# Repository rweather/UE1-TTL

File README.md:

UE1 Computer in TTL
===================

## What is this?

This is an implementation of the [Usagi Electric UE1 vacuum tube computer architecture](https://github.com/Nakazoto/UEVTC/wiki)
in TTL logic.  It runs the same code as the original.

Here is the top and bottom of the version 1 prototype, just after running the
Fibonacci example (click for a larger image):

I made some mistakes in the version 1 prototype that needed bodging.
The schematics and gerbers below have been updated to include the fixes.

## Specifications

* TTL logic, 555 timers, and EEPROM chips only.  No cheating with a modern
  microcontroller running an emulator.
* 1-bit processor core based on the UE14500 instruction set.
* 8-bit scratch register (general-purpose RAM).
* 8-bit output register.
* 7-bit input register.
* EEPROM that stores up to 8 program "tapes", each up to 4096 instructions.
  DIP switches select which program to run.
* 555-based clock that runs at frequencies between 0.7Hz and 480Hz.
* Run, Halt, and Reset buttons to control the computer.
* Blinkenlichten!
* Bell buzzer.
* Runs off a single 5V DC supply.

The computer is split across three PCB's, because:

* PCB's less than 100mm x 100mm in size are cheaper to get made.
* The aspect ratio of the boards is close to those of the wooden backing
  boards in the original UE1 to provide a similar visual aesthetic
  (although I need 3 boards compared with the original 2).
* It is easier to upgrade one of the boards without having to re-spin
  the other boards.

## Technical information

* [Theory of operation](doc/theory_of_operation.md)
* [Signals on the edge connectors](doc/edge_connectors.md)

### Clock and front panel board

* [Schematics](schematics/UE1-TTL-Clock/PDF/UE1-TTL-Clock.pdf)
* [Gerbers](schematics/UE1-TTL-Clock/Gerber)
* [Assembling and testing](doc/testing_clock.md)
* [Version 1 mistakes](doc/testing_clock.md#version-1-mistakes)

### Processor board

* [Schematics](schematics/UE14500-TTL/PDF/UE14500-TTL.pdf)
* [Gerbers](schematics/UE14500-TTL/Gerber)
* [Assembling and testing](doc/testing_processor.md)
* [Version 1 mistakes](doc/testing_processor.md#version-1-mistakes)

### Memory and I/O board

* [Schematics](schematics/UE1-TTL-Memory/PDF/UE1-TTL-Memory.pdf)
* [Gerbers](schematics/UE1-TTL-Memory/Gerber)
* [Assembling and testing](doc/testing_memory.md)
* [Version 1 mistakes](doc/testing_memory.md#version-1-mistakes)

## Programming the computer

To reprogram the computer it is necessary to remove the 32K AT28C256 tape
EEPROM from the memory board and flash in a new set of tape images using an
EEPROM programmer.

There can be up to 8 programs in the EEPROM, with DIP switches to select
which program to run.  Each program is up to 4096 instructions long,
which corresponds to about 10m of paper tape.  Each instruction consists
of a 4-bit opcode and a 4-bit memory address just like in the vacuum tube
based UE1.

Pad shorter programs with NOP0 instructions or replicate the program
multiple times to fill up the 4096 bytes of space.  There is a new
"rewind" opcode that can be used to loop short programs without
excessive NOP0's.  See the next section.

The "programs" directory contains some sample programs, together with a
Python script to pack up to 8 binaries into a single 32K EEPROM image.

## Instruction set

This computer uses the same [instruction set](https://github.com/Nakazoto/UEVTC/wiki/UE14500-Processor)
as the original computer.  The only difference is the introduction of a
"rewind" opcode which is encoded as "NOP0" with a memory address between
8 and 15 - bytes $08 to $0F in hexadecimal.

The rewind opcode causes the 12-bit program counter to reset back to 0
immediately, rather than waiting for the program counter to wrap around.
This can be convenient for short looping programs to avoid a long wait
for the loop to restart.

## Parts lists

In the parts lists below, "RLED" refers to the inline series resistor
for the LED's.  The value depends upon the type of LED you have, and can
be calculated from the LED's voltage drop (VLED) and rated current (ILED)
as follows:

    RLED = (5 - VLED) / ILED

For example, if your LED is rated for 1.9V and 10mA, then RLED should be
at least (5 - 1.9) / 0.01 = 310 ohms.  A 330 ohm resistor will do.
I recommend using LED's with 2mA or less current rating to avoid putting
too much strain on the TTL logic outputs.  I used 2mA LED's and RLED =
1800 ohms.

The IC's are listed as 74LS series, but you can use 74HC series instead.
Use the same series for all chips.

Parts lists for individual boards are listed first, and then a combined
parts list for the whole computer.

### Clock and front panel board

* 2 x 555 timer
* 1 x 74HC4017 decade counter
* 1 x 74LS74 dual D flip-flop
* 1 x 74LS02 quad NOR gate
* 1 x 74LS132 quad NAND gate with Schmitt trigger
* 2 x 10nF ceramic or monolithic capacitor
* 4 x 100nF ceramic or monolithic capacitor
* 4 x 1uF ceramic or monolithic capacitor
* 1 x 1M trimpot
* 2 x 1K resistor
* 1 x 3K3 resistor
* 1 x 4K7 resistor
* 1 x 10K resistor
* 1 x 100K resistor
* 22 x RLED resistor
* 22 x 3mm LED (colour of your choice)
* 1 x Buzzer with 7.6mm pin pitch
* 3 x 6mm momentary push button
* 1 x 3-way 2.54mm pin header
* 1 x 2-way 2.54mm pin header
* 2 x 2.54mm jumper
* 2 x 36-pin right-angle terminal header
* 2 x 8-pin DIP socket
* 3 x 14-pin DIP socket
* 1 x 16-pin DIP socket

### Processor board

* 3 x 74LS00 quad NAND gate
* 3 x 74LS02 quad NOR gate
* 2 x 74LS08 quad AND gate
* 3 x 74LS74 dual D flip-flop
* 1 x 74LS86 quad XOR gate
* 2 x 74LS138 3-to-8 line decoder
* 1 x 74LS251 8-line to 1-line multiplexer
* 1 x 74LS374 8-bit register
* 1 x 100uF electrolytic capacitor
* 1 x 1uF ceramic or monolithic capacitor
* 16 x 100nF ceramic or monolithic capacitor
* 1 x 10K resistor
* 1 x SPDT 2.54mm slide switch
* 1 x 2.5mm DC barrel jack
* 2 x 36-pin right-angle terminal socket
* 12 x 14-pin DIP socket
* 3 x 16-pin DIP socket
* 1 x 20-pin DIP socket

### Memory and I/O board

* 1 x AT28C256 32K x 8 EEPROM
* 1 x 74LS32 quad OR gate
* 1 x 74LS139 dual 2-to-4 line decoder
* 2 x 74LS251 8-line to 1-line multiplexer
* 2 x 74LS259 8-bit addressable latch
* 2 x 74LS393 dual binary 4-bit counter
* 9 x 100nF ceramic or monolithic capacitor
* 1 x 10K resistor
* 10 x 100K resistor
* 8 x RLED resistor
* 8 x 3mm LED (colour of your choice)
* 1 x 8-way DIP switches
* 1 x 3-way DIP switches
* 2 x 36-pin right-angle terminal header
* 3 x 14-pin DIP socket
* 5 x 16-pin DIP socket
* 1 x 28-pin DIP socket (15.24mm pitch width)

I recommend using a socket for the 28-pin EEPROM even if you don't use
sockets for the other chips.  You will need to easily remove the EEPROM to
reprogram it.

## Combined part list

This section combines all three lists into one to make it easier to
order the parts for the whole computer.  As stated before, 74HC series
chips can be used in place of 74LS.

* 1 x AT28C256 32K x 8 EEPROM
* 2 x 555 timer
* 1 x 74HC4017 decade counter
* 3 x 74LS00 quad NAND gate
* 4 x 74LS02 quad NOR gate
* 2 x 74LS08 quad AND gate
* 1 x 74LS32 quad OR gate
* 4 x 74LS74 dual D flip-flop
* 1 x 74LS86 quad XOR gate
* 1 x 74LS132 quad NAND gate with Schmitt trigger
* 2 x 74LS138 3-to-8 line decoder
* 1 x 74LS139 dual 2-to-4 line decoder
* 3 x 74LS251 8-line to 1-line multiplexer
* 2 x 74LS259 8-bit addressable latch
* 1 x 74LS374 8-bit register
* 2 x 74LS393 dual binary 4-bit counter
* 1 x 100uF electrolytic capacitor
* 5 x 1uF ceramic or monolithic capacitor
* 2 x 10nF ceramic or monolithic capacitor
* 29 x 100nF ceramic or monolithic capacitor
* 1 x 1M trimpot
* 2 x 1K resistor
* 1 x 3K3 resistor
* 1 x 4K7 resistor
* 3 x 10K resistor
* 11 x 100K resistor
* 30 x RLED resistor
* 30 x 3mm LED (colour of your choice)
* 1 x SPDT 2.54mm slide switch
* 1 x 2.5mm DC barrel jack
* 1 x Buzzer with 7.6mm pin pitch
* 3 x 6mm momentary push button
* 1 x 3-way 2.54mm pin header
* 1 x 2-way 2.54mm pin header
* 2 x 2.54mm jumper
* 1 x 8-way DIP switches
* 1 x 3-way DIP switches
* 4 x 36-pin terminal header (for clock and memory boards)
* 2 x 36-pin terminal socket (for CPU board)
* 2 x 8-pin DIP socket
* 18 x 14-pin DIP socket
* 9 x 16-pin DIP socket
* 1 x 20-pin DIP socket
* 1 x 28-pin DIP socket (15.24mm pitch width)

I recommend using a socket for the 28-pin EEPROM even if you don't use
sockets for the other chips.  You will need to easily remove the EEPROM to
reprogram it.

## License

<p xmlns:cc="http://creativecommons.org/ns#" xmlns:dct="http://purl.org/dc/terms/"><span property="dct:title">UE1 TTL</span> by <span property="cc:attributionName">Rhys Weatherley</span> is licensed under <a href="http://creativecommons.org/licenses/by-nc-sa/4.0/?ref=chooser-v1" target="_blank" rel="license noopener noreferrer" style="display:inline-block;">Attribution-NonCommercial-ShareAlike 4.0 International</a></p>

## Contact

For more information on this project, to report bugs, or to suggest
improvements, please contact the author Rhys Weatherley via
[email](mailto:rhys.weatherley@gmail.com).

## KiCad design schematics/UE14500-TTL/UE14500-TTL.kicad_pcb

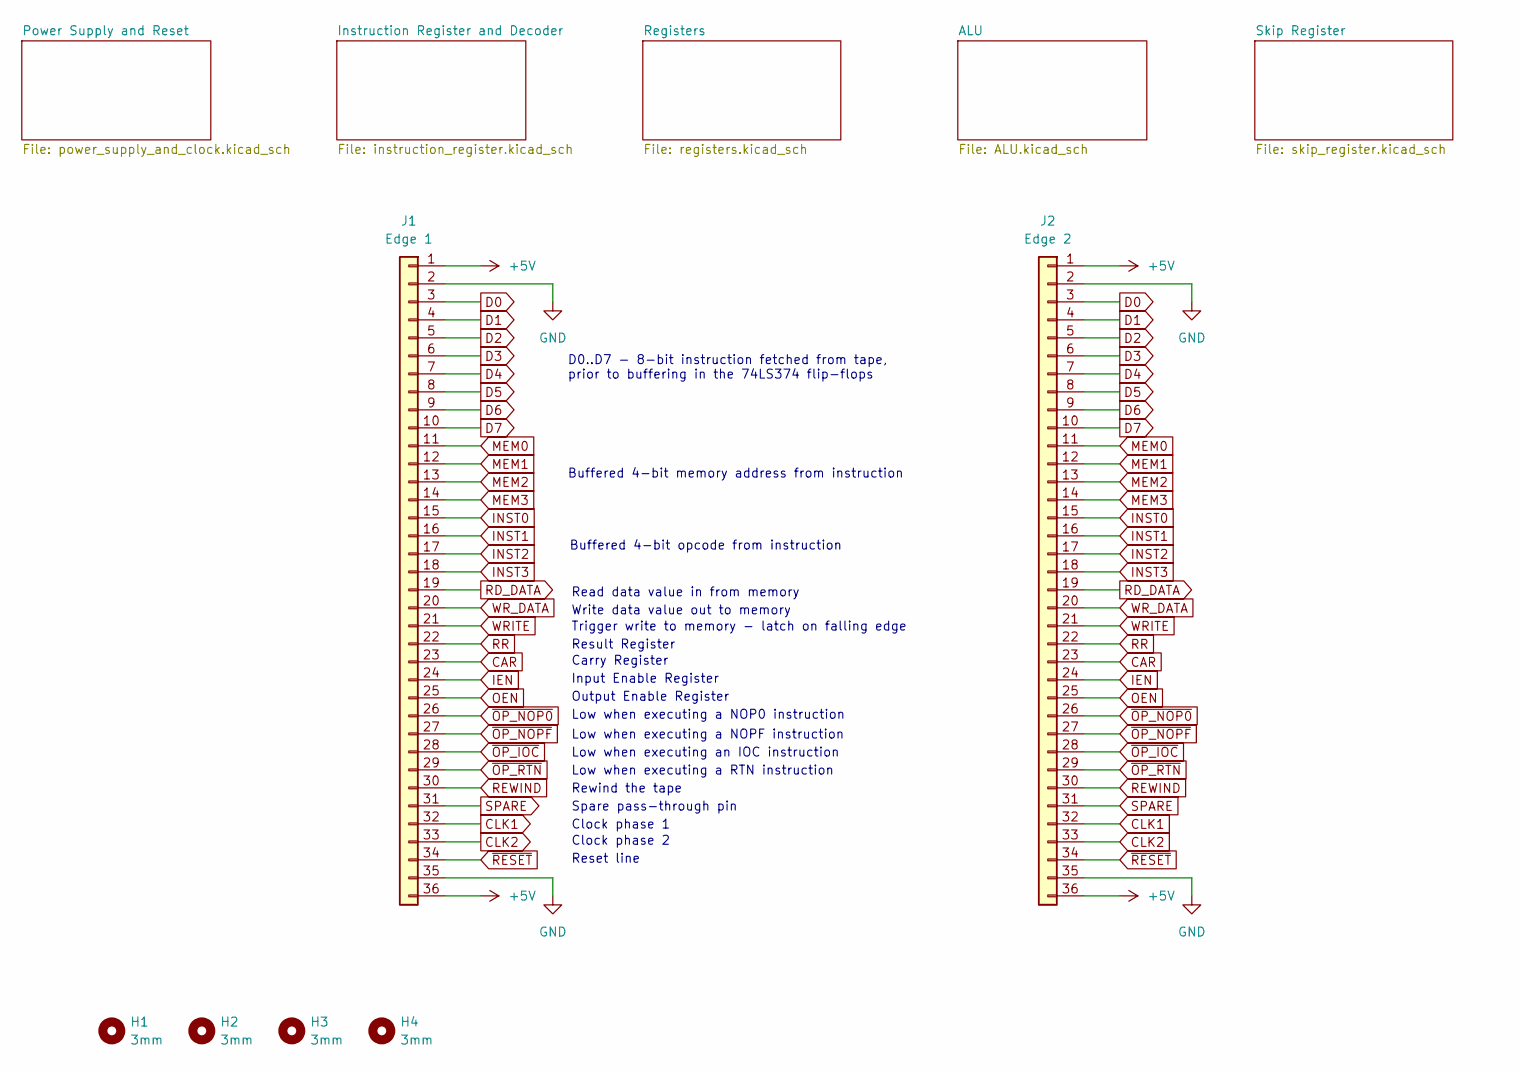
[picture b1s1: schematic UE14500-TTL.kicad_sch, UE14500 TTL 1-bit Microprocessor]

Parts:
H1, H2, H3, H4: 3mm; MountingHole_3mm
J1: Edge 1; PinSocket_1x36_P2.54mm_Horizontal
J2: Edge 2; PinHeader_1x36_P2.54mm_Horizontal

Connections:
+5V: J1.1, J1.36, J2.1, J2.36; also elsewhere on the board
CAR: J1.23, J2.23; also elsewhere on the board
CLK1: J1.32, J2.32; also elsewhere on the board
CLK2: J1.33, J2.33; also elsewhere on the board
D0: J1.3, J2.3; also elsewhere on the board
D1: J1.4, J2.4; also elsewhere on the board
D2: J1.5, J2.5; also elsewhere on the board
D3: J1.6, J2.6; also elsewhere on the board
D4: J1.7, J2.7; also elsewhere on the board
D5: J1.8, J2.8; also elsewhere on the board
D6: J1.9, J2.9; also elsewhere on the board
D7: J1.10, J2.10; also elsewhere on the board
GND: J1.2, J1.35, J2.2, J2.35; also elsewhere on the board
IEN: J1.24, J2.24; also elsewhere on the board
INST0: J1.15, J2.15; also elsewhere on the board
INST1: J1.16, J2.16; also elsewhere on the board
INST2: J1.17, J2.17; also elsewhere on the board
INST3: J1.18, J2.18; also elsewhere on the board
MEM0: J1.11, J2.11; also elsewhere on the board
MEM1: J1.12, J2.12; also elsewhere on the board
MEM2: J1.13, J2.13; also elsewhere on the board
MEM3: J1.14, J2.14; also elsewhere on the board
OEN: J1.25, J2.25; also elsewhere on the board
RD_DATA: J1.19, J2.19; also elsewhere on the board
REWIND: J1.30, J2.30; also elsewhere on the board
RR: J1.22, J2.22; also elsewhere on the board
SPARE: J1.31, J2.31
WRITE: J1.21, J2.21; also elsewhere on the board
WR_DATA: J1.20, J2.20; also elsewhere on the board
~OP_IOC: J1.28, J2.28; also elsewhere on the board
~OP_NOP0: J1.26, J2.26; also elsewhere on the board
~OP_NOPF: J1.27, J2.27; also elsewhere on the board
~OP_RTN: J1.29, J2.29; also elsewhere on the board
~RESET: J1.34, J2.34; also elsewhere on the board

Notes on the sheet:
Rewind the tape
Clock phase 2
Clock phase 1
Spare pass-through pin
Result Register
Output Enable Register
Low when executing a RTN instruction
Buffered 4-bit opcode from instruction
Low when executing a NOP0 instruction
Low when executing a NOPF instruction
D0..D7 - 8-bit instruction fetched from tape, prior to buffering in the 74LS374 flip-flops
Trigger write to memory - latch on falling edge
Reset line
Write data value out to memory
Input Enable Register
Read data value in from memory
Low when executing an IOC instruction
Carry Register
Buffered 4-bit memory address from instruction

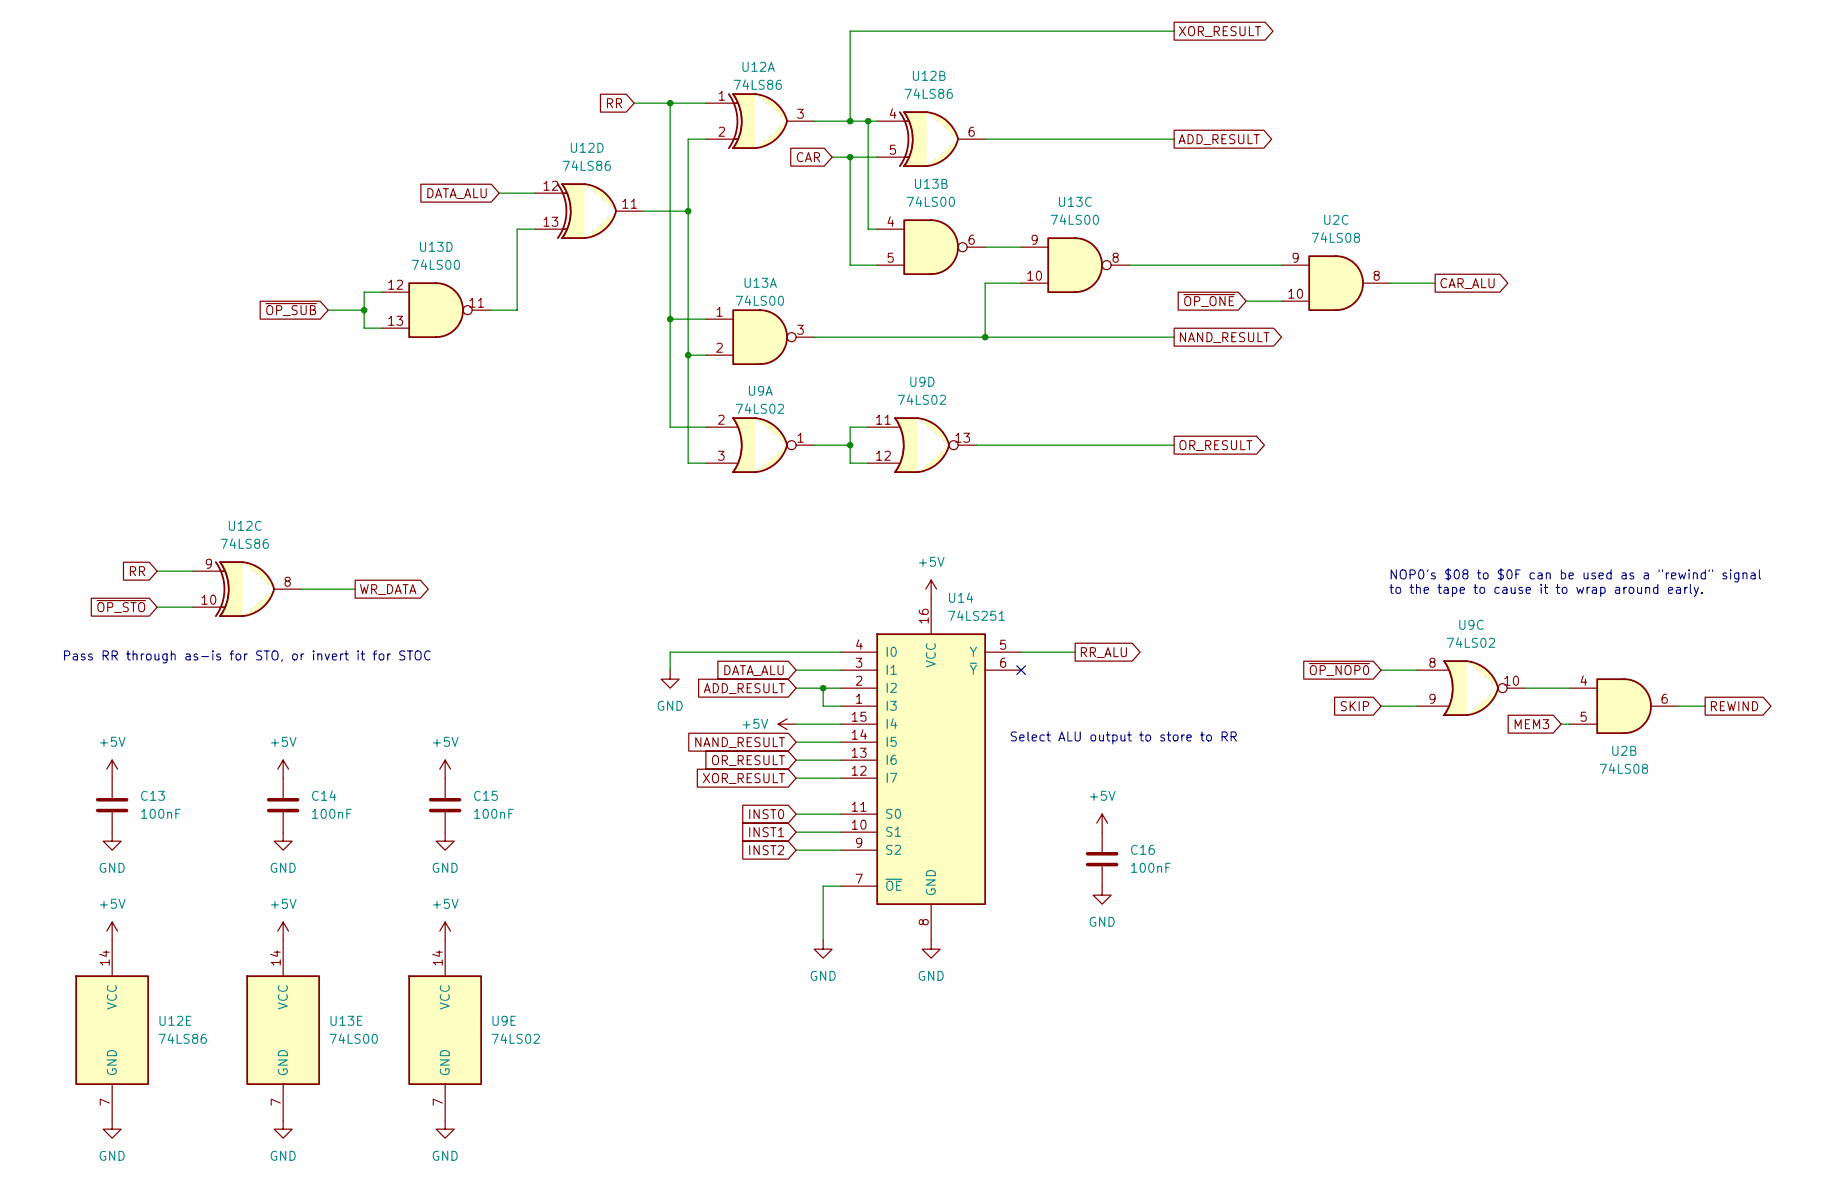
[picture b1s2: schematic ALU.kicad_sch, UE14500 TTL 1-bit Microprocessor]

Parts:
C13, C14, C15, C16: 100nF; C_Disc_D5.0mm_W2.5mm_P5.00mm
U2: 74LS08; DIP-14_W7.62mm
U9: 74LS02; DIP-14_W7.62mm
U12: 74LS86; DIP-14_W7.62mm
U13: 74LS00; DIP-14_W7.62mm
U14: 74LS251; DIP-16_W7.62mm

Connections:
+5V: C13.1, C14.1, C15.1, C16.1, U9.14 (VCC), U12.14 (VCC), U13.14 (VCC), U14.15 (I4), U14.16 (VCC); also elsewhere on the board
ADD_RESULT: U12.6, U14.1 (I3), U14.2 (I2)
CAR: U12.5, U13.5; also elsewhere on the board
CAR_ALU: U2.8; also elsewhere on the board
DATA_ALU: U12.12, U14.3 (I1); also elsewhere on the board
GND: C13.2, C14.2, C15.2, C16.2, U9.7 (GND), U12.7 (GND), U13.7 (GND), U14.4 (I0), U14.7 (~OE), U14.8 (GND); also elsewhere on the board
INST0: U14.11 (S0); also elsewhere on the board
INST1: U14.10 (S1); also elsewhere on the board
INST2: U14.9 (S2); also elsewhere on the board
MEM3: U2.5; also elsewhere on the board
NAND_RESULT: U13.3, U13.10, U14.14 (I5)
unnamed: U2.4, U9.10
unnamed: U9.1, U9.11, U9.12
unnamed: U9.3, U12.2, U12.11, U13.2
unnamed: U12.13, U13.11
unnamed: U13.6, U13.9
unnamed: U2.9, U13.8
OR_RESULT: U9.13, U14.13 (I6)
REWIND: U2.6; also elsewhere on the board
RR: U9.2, U12.1, U12.9, U13.1; also elsewhere on the board
RR_ALU: U14.5 (Y); also elsewhere on the board
SKIP: U9.9; also elsewhere on the board
WR_DATA: U12.8; also elsewhere on the board
XOR_RESULT: U12.3, U12.4, U13.4, U14.12 (I7)
~OP_NOP0: U9.8; also elsewhere on the board
~OP_ONE: U2.10; also elsewhere on the board
~OP_STO: U12.10; also elsewhere on the board
~OP_SUB: U13.12, U13.13; also elsewhere on the board

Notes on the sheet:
Select ALU output to store to RR
Pass RR through as-is for STO, or invert it for STOC
NOP0's $08 to $0F can be used as a "rewind" signal to the tape to cause it to wrap around early.

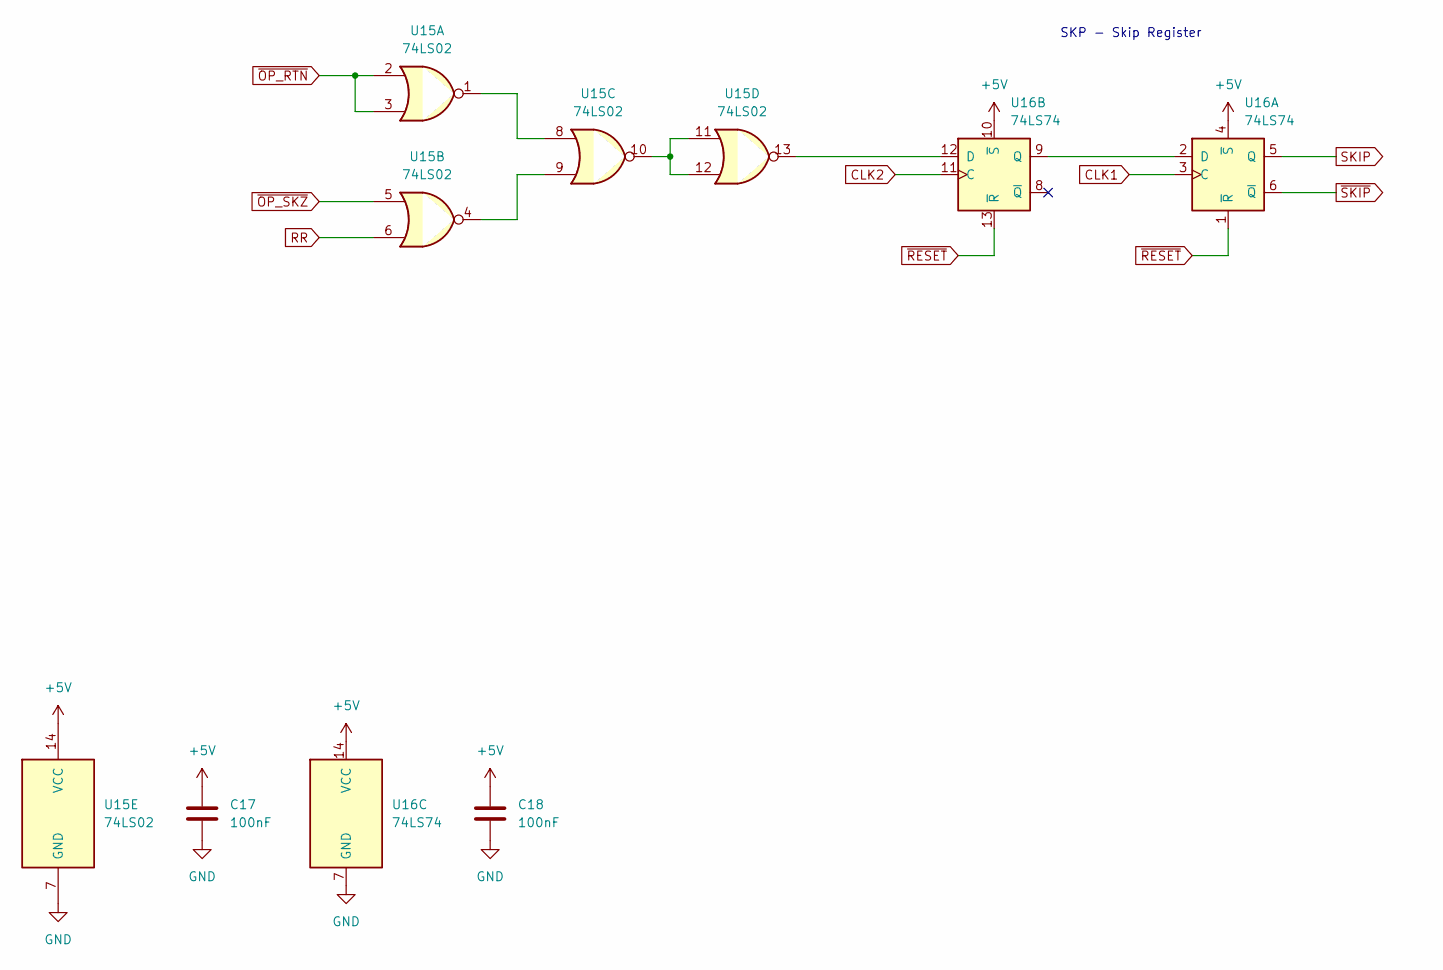
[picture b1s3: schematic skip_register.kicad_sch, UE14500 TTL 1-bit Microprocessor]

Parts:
C17, C18: 100nF; C_Disc_D5.0mm_W2.5mm_P5.00mm
U15: 74LS02; DIP-14_W7.62mm
U16: 74LS74; DIP-14_W7.62mm

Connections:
+5V: C17.1, C18.1, U15.14 (VCC), U16.4 (~S), U16.10 (~S), U16.14 (VCC); also elsewhere on the board
CLK1: U16.3 (C); also elsewhere on the board
CLK2: U16.11 (C); also elsewhere on the board
GND: C17.2, C18.2, U15.7 (GND), U16.7 (GND); also elsewhere on the board
unnamed: U15.1, U15.8
unnamed: U15.4, U15.9
unnamed: U15.10, U15.11, U15.12
unnamed: U16.2 (D), U16.9 (Q)
unnamed: U15.13, U16.12 (D)
RR: U15.6; also elsewhere on the board
SKIP: U16.5 (Q); also elsewhere on the board
~OP_RTN: U15.2, U15.3; also elsewhere on the board
~OP_SKZ: U15.5; also elsewhere on the board
~RESET: U16.1 (~R), U16.13 (~R); also elsewhere on the board
~SKIP: U16.6 (~Q); also elsewhere on the board

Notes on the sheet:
SKP - Skip Register

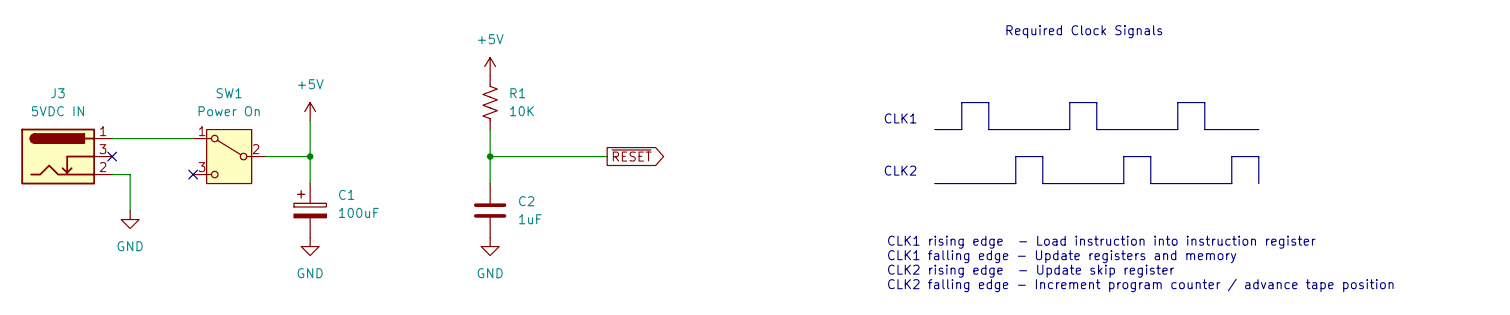
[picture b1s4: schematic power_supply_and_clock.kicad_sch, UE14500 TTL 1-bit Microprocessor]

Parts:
C1: 100uF; CP_Radial_D6.3mm_P2.50mm
C2: 1uF; C_Disc_D5.0mm_W2.5mm_P5.00mm
J3: 5VDC IN; BarrelJack_Horizontal
R1: 10K; R_Axial_DIN0207_L6.3mm_D2.5mm_P10.16mm_Horizontal
SW1: Power On; SW_Slide-03_Wuerth-WS-SLTV_10x2.5x6.4_P2.54mm

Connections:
+5V: C1.1, R1.2, SW1.2 (B); also elsewhere on the board
GND: C1.2, C2.2, J3.2; also elsewhere on the board
unnamed: J3.1, SW1.1 (A)
~RESET: C2.1, R1.1; also elsewhere on the board

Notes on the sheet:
CLK2
CLK1
CLK1 rising edge - Load instruction into instruction register CLK1 falling edge - Update registers and memory CLK2 rising edge - Update skip register CLK2 falling edge - Increment program counter / advance tape position
Required Clock Signals

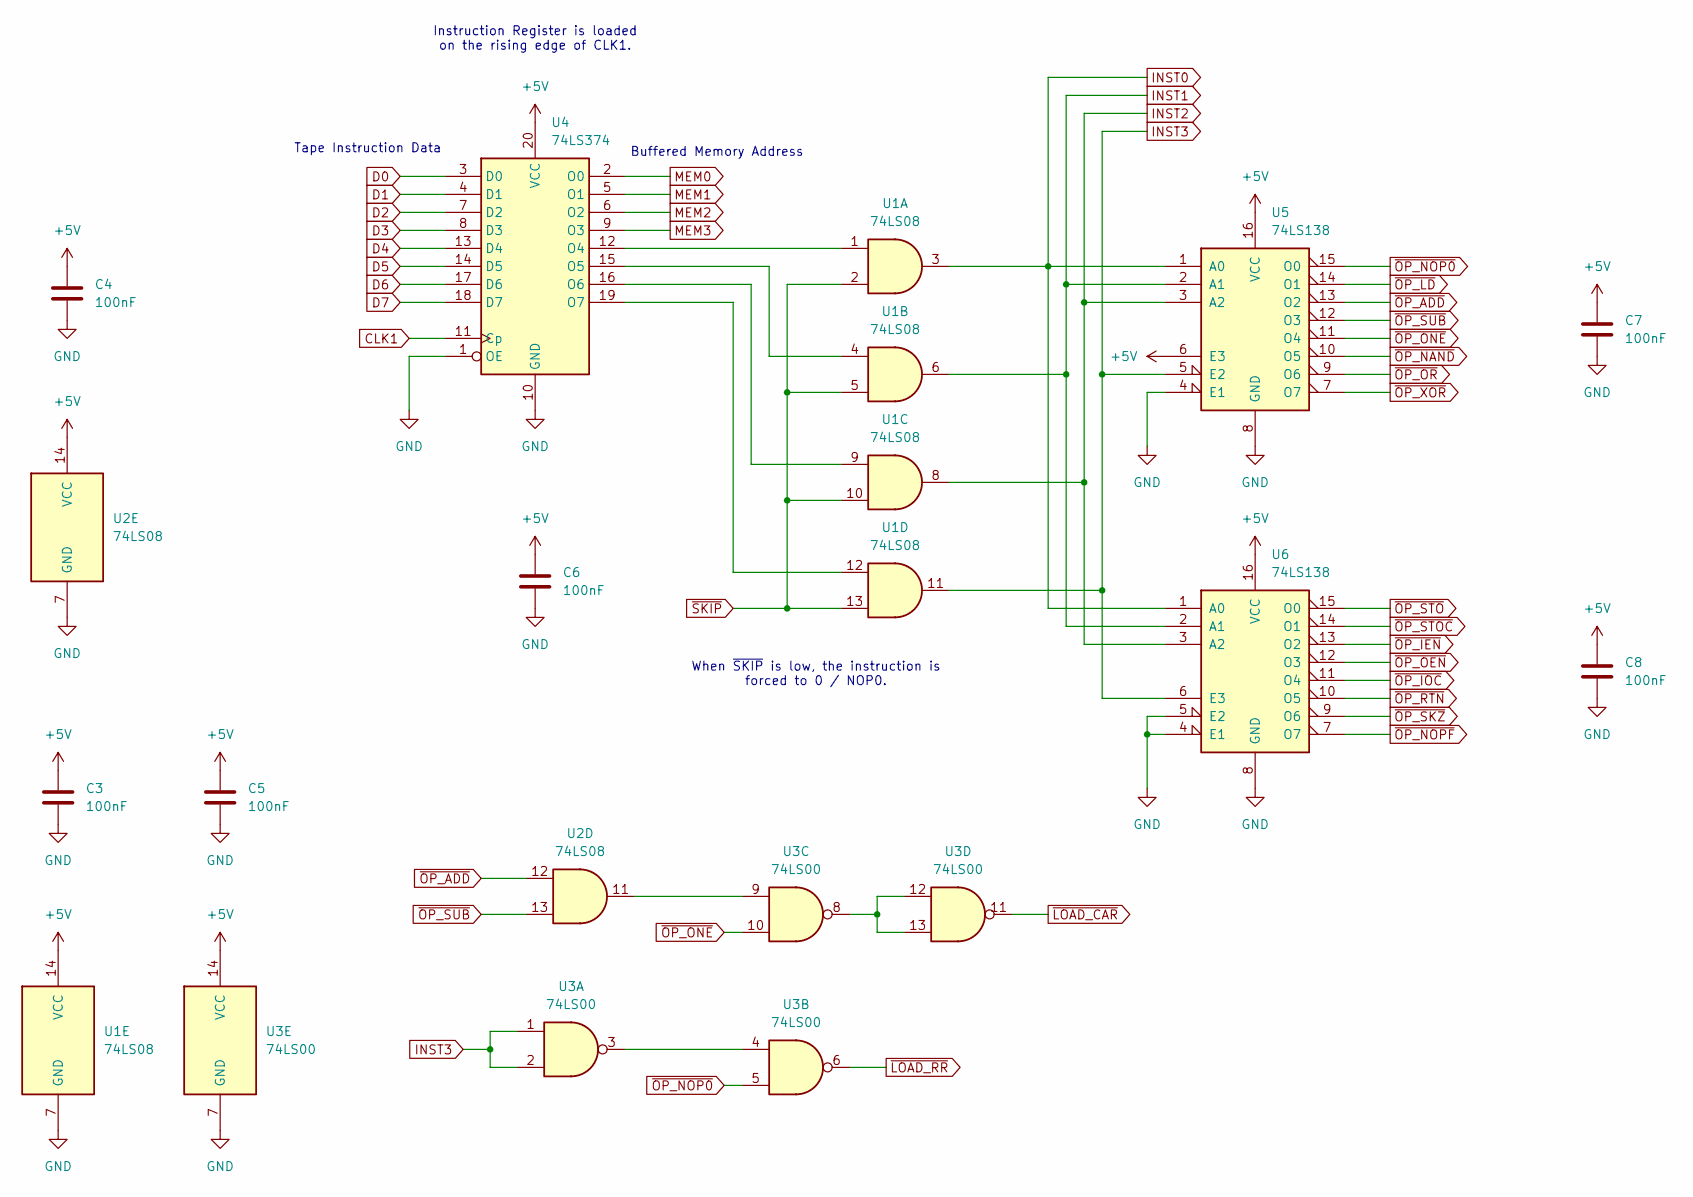
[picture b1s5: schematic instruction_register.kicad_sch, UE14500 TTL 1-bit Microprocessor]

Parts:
C3, C4, C5, C6, C7, C8: 100nF; C_Disc_D5.0mm_W2.5mm_P5.00mm
U1, U2: 74LS08; DIP-14_W7.62mm
U3: 74LS00; DIP-14_W7.62mm
U4: 74LS374; DIP-20_W7.62mm
U5, U6: 74LS138; DIP-16_W7.62mm

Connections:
+5V: C3.1, C4.1, C5.1, C6.1, C7.1, C8.1, U1.14 (VCC), U2.14 (VCC), U3.14 (VCC), U4.20 (VCC), U5.6 (E3), U5.16 (VCC), U6.16 (VCC); also elsewhere on the board
CLK1: U4.11 (Cp); also elsewhere on the board
D0: U4.3 (D0); also elsewhere on the board
D1: U4.4 (D1); also elsewhere on the board
D2: U4.7 (D2); also elsewhere on the board
D3: U4.8 (D3); also elsewhere on the board
D4: U4.13 (D4); also elsewhere on the board
D5: U4.14 (D5); also elsewhere on the board
D6: U4.17 (D6); also elsewhere on the board
D7: U4.18 (D7); also elsewhere on the board
GND: C3.2, C4.2, C5.2, C6.2, C7.2, C8.2, U1.7 (GND), U2.7 (GND), U3.7 (GND), U4.1 (OE), U4.10 (GND), U5.4 (E1), U5.8 (GND), U6.4 (E1), U6.5 (E2), U6.8 (GND); also elsewhere on the board
INST0: U1.3, U5.1 (A0), U6.1 (A0); also elsewhere on the board
INST1: U1.6, U5.2 (A1), U6.2 (A1); also elsewhere on the board
INST2: U1.8, U5.3 (A2), U6.3 (A2); also elsewhere on the board
INST3: U1.11, U3.1, U3.2, U5.5 (E2), U6.6 (E3); also elsewhere on the board
MEM0: U4.2 (O0); also elsewhere on the board
MEM1: U4.5 (O1); also elsewhere on the board
MEM2: U4.6 (O2); also elsewhere on the board
MEM3: U4.9 (O3); also elsewhere on the board
unnamed: U2.11, U3.9
unnamed: U3.3, U3.4
unnamed: U3.8, U3.12, U3.13
unnamed: U1.1, U4.12 (O4)
unnamed: U1.4, U4.15 (O5)
unnamed: U1.9, U4.16 (O6)
unnamed: U1.12, U4.19 (O7)
~LOAD_CAR: U3.11; also elsewhere on the board
~LOAD_RR: U3.6; also elsewhere on the board
~OP_ADD: U2.12, U5.13 (O2)
~OP_IEN: U6.13 (O2); also elsewhere on the board
~OP_IOC: U6.11 (O4); also elsewhere on the board
~OP_LD: U5.14 (O1)
~OP_NAND: U5.10 (O5)
~OP_NOP0: U3.5, U5.15 (O0); also elsewhere on the board
~OP_NOPF: U6.7 (O7); also elsewhere on the board
~OP_OEN: U6.12 (O3); also elsewhere on the board
~OP_ONE: U3.10, U5.11 (O4); also elsewhere on the board
~OP_OR: U5.9 (O6)
~OP_RTN: U6.10 (O5); also elsewhere on the board
~OP_SKZ: U6.9 (O6); also elsewhere on the board
~OP_STOC: U6.14 (O1); also elsewhere on the board
~OP_STO: U6.15 (O0); also elsewhere on the board
~OP_SUB: U2.13, U5.12 (O3); also elsewhere on the board
~OP_XOR: U5.7 (O7)
~SKIP: U1.2, U1.5, U1.10, U1.13; also elsewhere on the board

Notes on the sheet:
Tape Instruction Data
When ~{SKIP} is low, the instruction is forced to 0 / NOP0.
Instruction Register is loaded on the rising edge of CLK1.
Buffered Memory Address

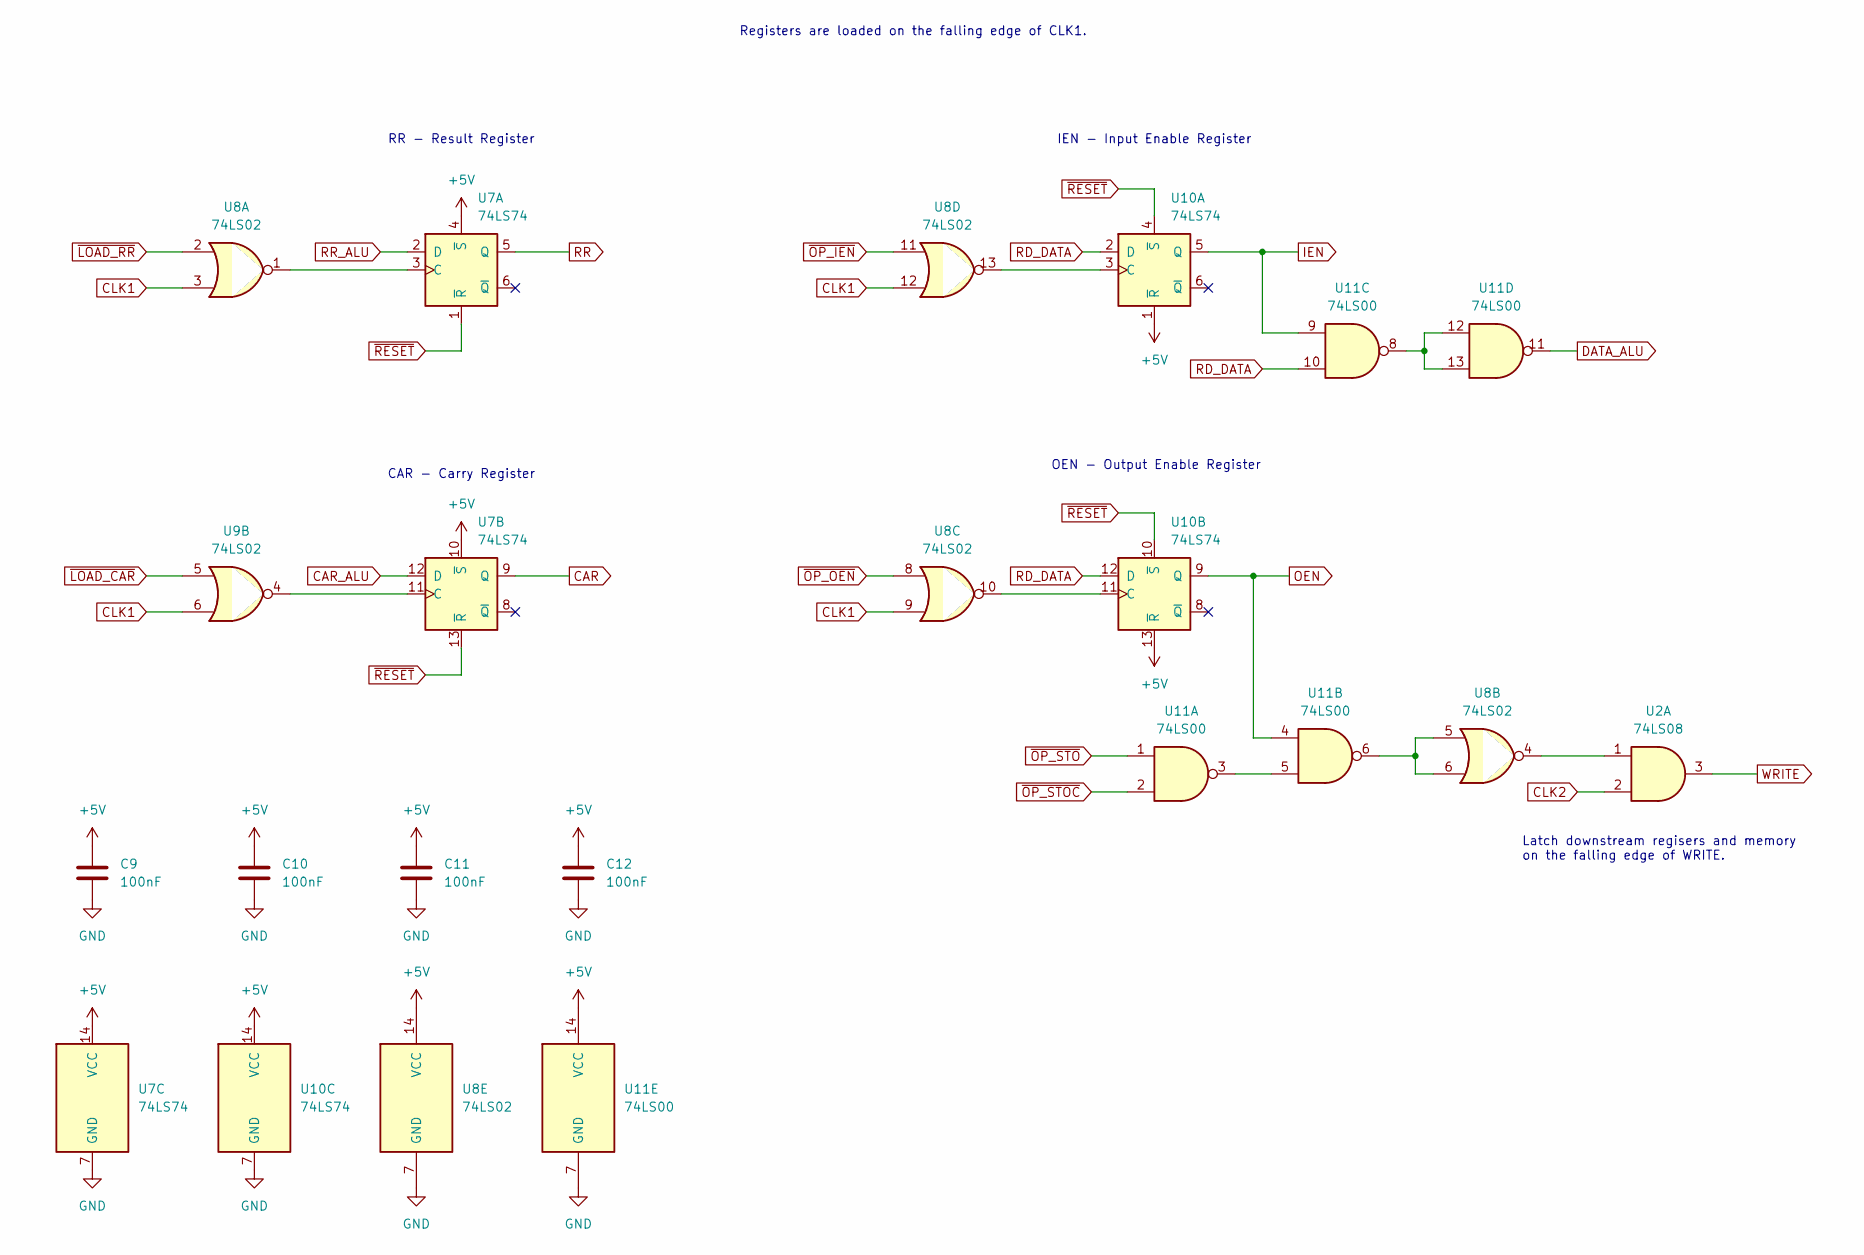
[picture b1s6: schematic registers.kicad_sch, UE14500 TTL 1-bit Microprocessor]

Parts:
C9, C10, C11, C12: 100nF; C_Disc_D5.0mm_W2.5mm_P5.00mm
U2: 74LS08; DIP-14_W7.62mm
U7, U10: 74LS74; DIP-14_W7.62mm
U8, U9: 74LS02; DIP-14_W7.62mm
U11: 74LS00; DIP-14_W7.62mm

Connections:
+5V: C9.1, C10.1, C11.1, C12.1, U7.4 (~S), U7.10 (~S), U7.14 (VCC), U8.14 (VCC), U10.1 (~R), U10.13 (~R), U10.14 (VCC), U11.14 (VCC); also elsewhere on the board
CAR: U7.9 (Q); also elsewhere on the board
CAR_ALU: U7.12 (D); also elsewhere on the board
CLK1: U8.3, U8.9, U8.12, U9.6; also elsewhere on the board
CLK2: U2.2; also elsewhere on the board
DATA_ALU: U11.11; also elsewhere on the board
GND: C9.2, C10.2, C11.2, C12.2, U7.7 (GND), U8.7 (GND), U10.7 (GND), U11.7 (GND); also elsewhere on the board
IEN: U10.5 (Q), U11.9; also elsewhere on the board
unnamed: U2.1, U8.4
unnamed: U7.3 (C), U8.1
unnamed: U7.11 (C), U9.4
unnamed: U8.13, U10.3 (C)
unnamed: U8.10, U10.11 (C)
unnamed: U11.3, U11.5
unnamed: U8.5, U8.6, U11.6
unnamed: U11.8, U11.12, U11.13
OEN: U10.9 (Q), U11.4; also elsewhere on the board
RD_DATA: U10.2 (D), U10.12 (D), U11.10; also elsewhere on the board
RR: U7.5 (Q); also elsewhere on the board
RR_ALU: U7.2 (D); also elsewhere on the board
WRITE: U2.3; also elsewhere on the board
~LOAD_CAR: U9.5; also elsewhere on the board
~LOAD_RR: U8.2; also elsewhere on the board
~OP_IEN: U8.11; also elsewhere on the board
~OP_OEN: U8.8; also elsewhere on the board
~OP_STOC: U11.2; also elsewhere on the board
~OP_STO: U11.1; also elsewhere on the board
~RESET: U7.1 (~R), U7.13 (~R), U10.4 (~S), U10.10 (~S); also elsewhere on the board

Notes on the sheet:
Registers are loaded on the falling edge of CLK1.
RR - Result Register
Latch downstream regisers and memory on the falling edge of WRITE.
IEN - Input Enable Register
OEN - Output Enable Register
CAR - Carry Register

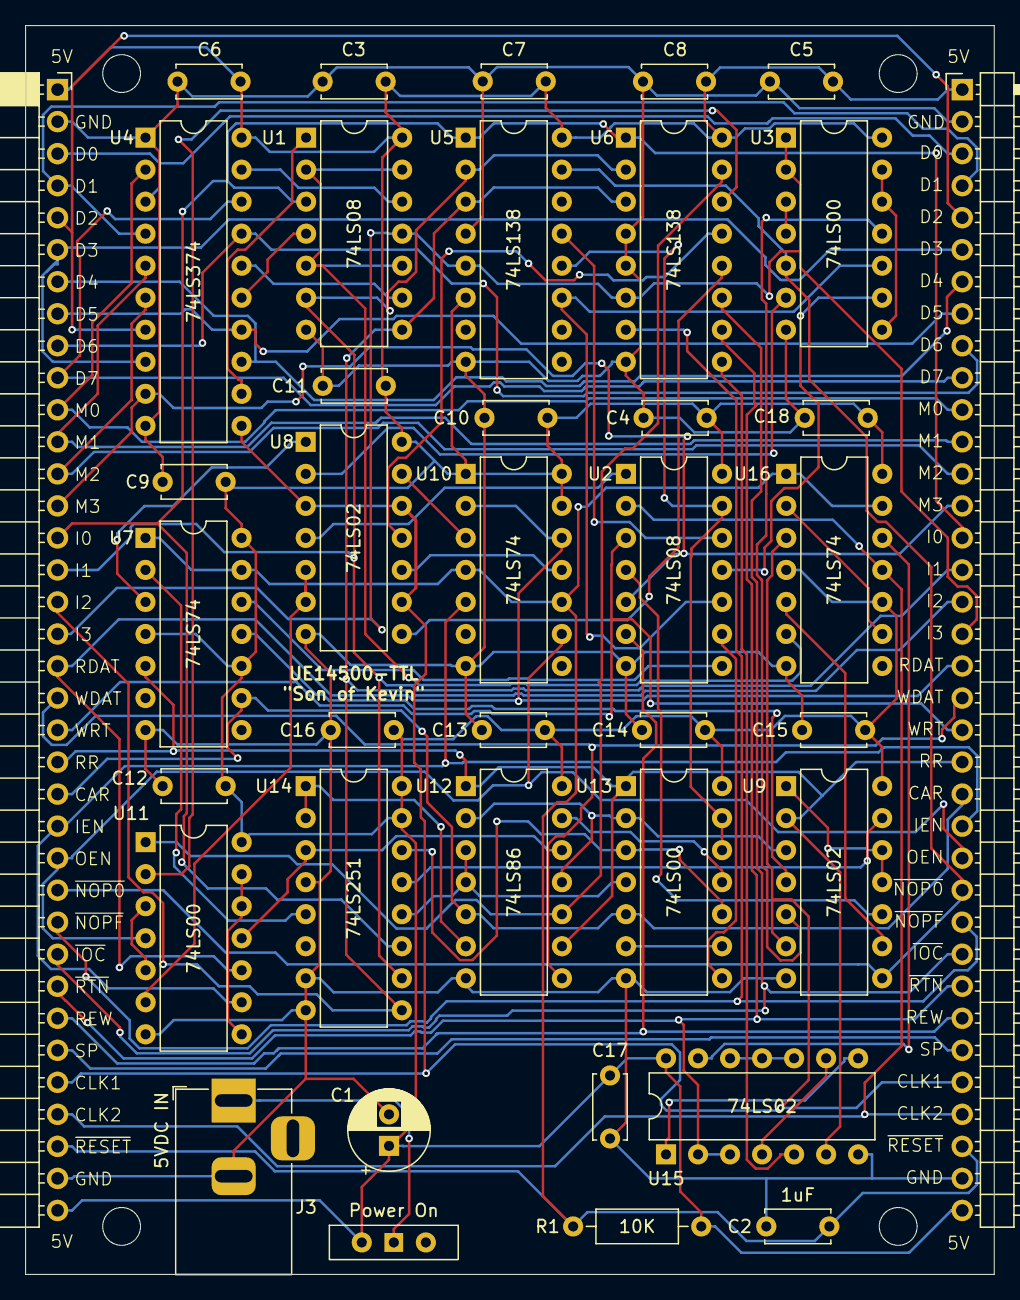
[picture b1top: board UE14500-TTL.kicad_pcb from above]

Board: 2 copper layers, 76.8 x 99.1 mm, 43 parts (0 on the bottom side), 80 nets.

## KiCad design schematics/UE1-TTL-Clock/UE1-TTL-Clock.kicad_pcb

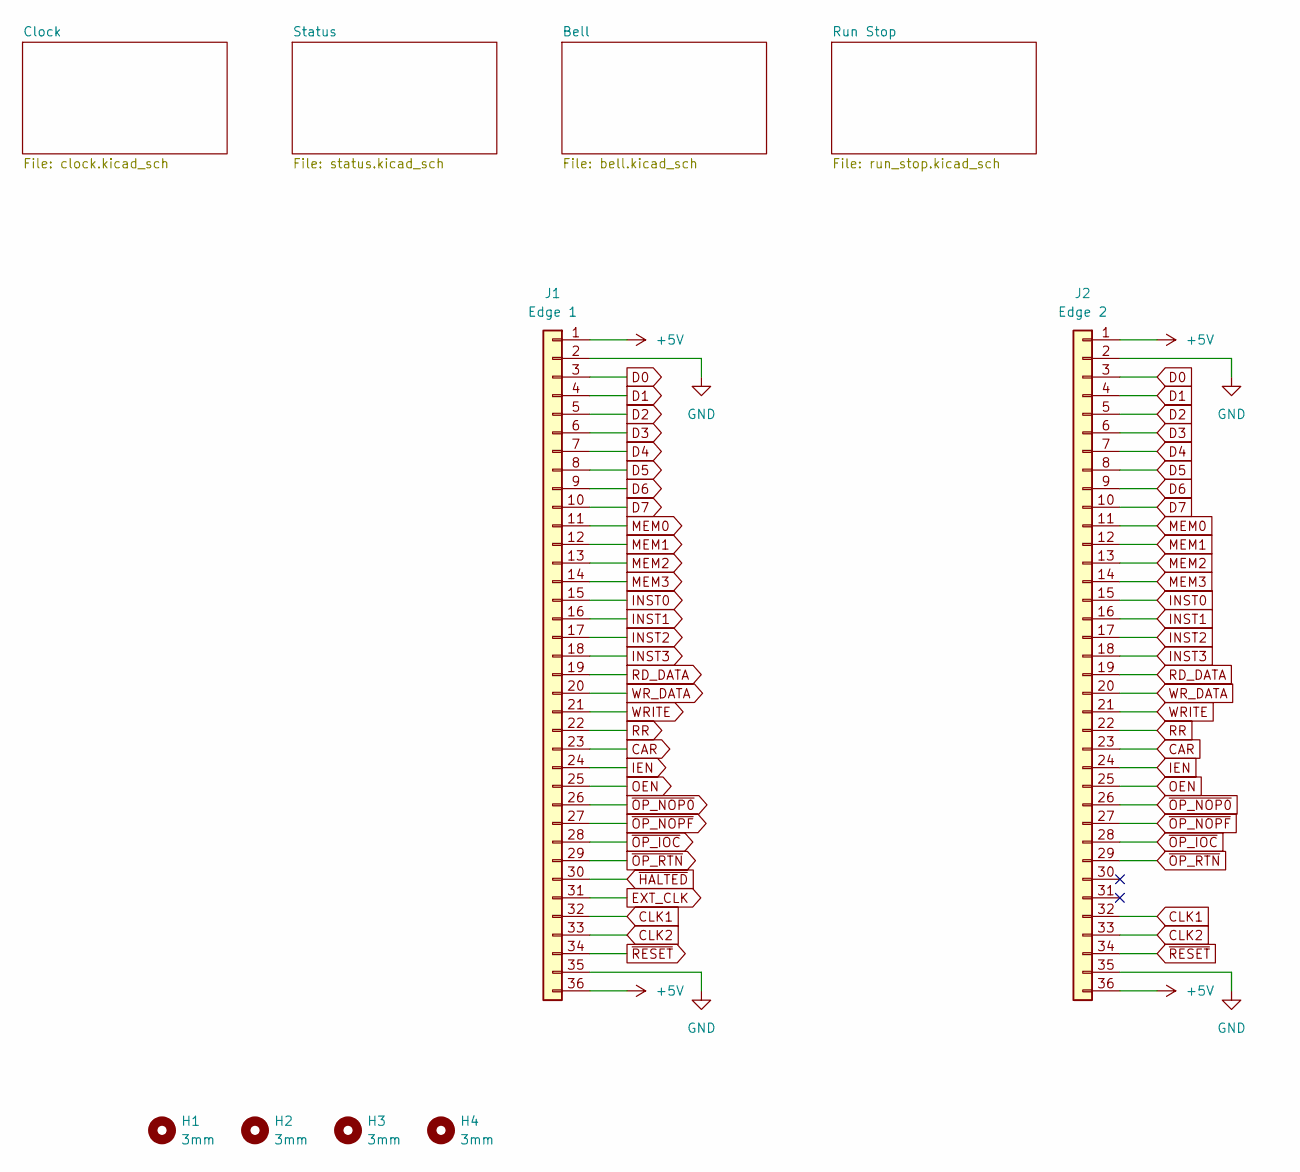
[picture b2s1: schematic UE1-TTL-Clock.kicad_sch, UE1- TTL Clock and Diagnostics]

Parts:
H1, H2, H3, H4: 3mm; MountingHole_3mm
J1: Edge 1; PinSocket_1x36_P2.54mm_Horizontal
J2: Edge 2; PinHeader_1x36_P2.54mm_Horizontal

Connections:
+5V: J1.1, J1.36, J2.1, J2.36; also elsewhere on the board
CAR: J1.23, J2.23; also elsewhere on the board
CLK1: J1.32, J2.32; also elsewhere on the board
CLK2: J1.33, J2.33; also elsewhere on the board
D0: J1.3, J2.3
D1: J1.4, J2.4
D2: J1.5, J2.5
D3: J1.6, J2.6
D4: J1.7, J2.7
D5: J1.8, J2.8
D6: J1.9, J2.9
D7: J1.10, J2.10
EXT_CLK: J1.31; also elsewhere on the board
GND: J1.2, J1.35, J2.2, J2.35; also elsewhere on the board
IEN: J1.24, J2.24; also elsewhere on the board
INST0: J1.15, J2.15; also elsewhere on the board
INST1: J1.16, J2.16; also elsewhere on the board
INST2: J1.17, J2.17; also elsewhere on the board
INST3: J1.18, J2.18; also elsewhere on the board
MEM0: J1.11, J2.11; also elsewhere on the board
MEM1: J1.12, J2.12; also elsewhere on the board
MEM2: J1.13, J2.13; also elsewhere on the board
MEM3: J1.14, J2.14; also elsewhere on the board
unnamed 51: J2.30; also elsewhere on the board
unnamed 52: J2.31; also elsewhere on the board
OEN: J1.25, J2.25; also elsewhere on the board
RD_DATA: J1.19, J2.19; also elsewhere on the board
RR: J1.22, J2.22; also elsewhere on the board
WRITE: J1.21, J2.21; also elsewhere on the board
WR_DATA: J1.20, J2.20; also elsewhere on the board
~HALTED: J1.30; also elsewhere on the board
~OP_IOC: J1.28, J2.28; also elsewhere on the board
~OP_NOP0: J1.26, J2.26; also elsewhere on the board
~OP_NOPF: J1.27, J2.27; also elsewhere on the board
~OP_RTN: J1.29, J2.29; also elsewhere on the board
~RESET: J1.34, J2.34; also elsewhere on the board

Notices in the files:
schematics/UE1-TTL-Clock-V1/bell.kicad_sch:
Copyright (c) 2025 Rhys Weatherley
